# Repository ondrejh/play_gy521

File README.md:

# play GY-521
playing with GY-521 module

## msp430 receiver
connect module to MSP-EXP430G2

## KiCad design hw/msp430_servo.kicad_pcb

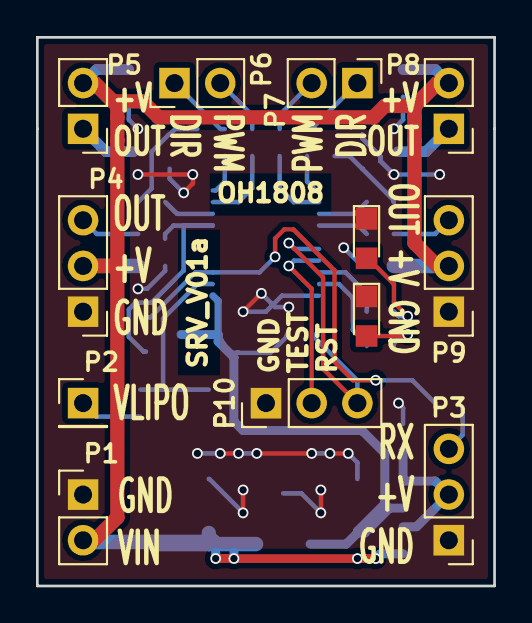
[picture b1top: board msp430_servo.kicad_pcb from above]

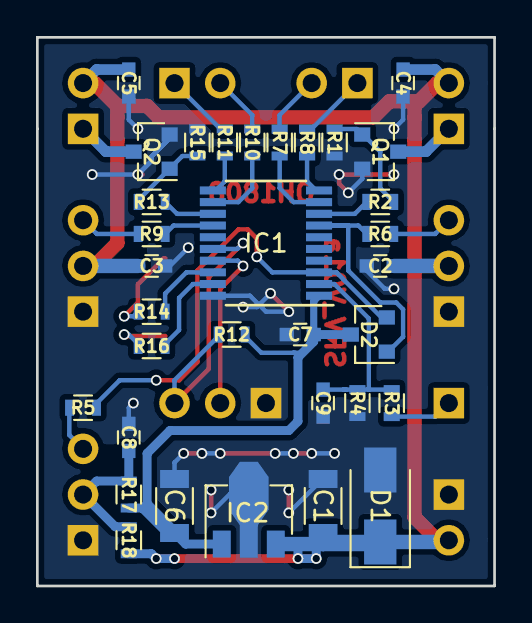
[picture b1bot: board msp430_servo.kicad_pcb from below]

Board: 2 copper layers, 25.4 x 30.5 mm, 45 parts (33 on the bottom side), 32 nets.

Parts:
C1, C6: 4u7; C_1206
C2, C3, C4, C5, C7, C8, C9: 100n; C_0603
D1: SMAJ5V0; D_SMA
D2: BAV70; SOT-23
IC1: MSP430G2553IPW20; TSSOP-20_4.4x6.5mm_Pitch0.65mm
IC2: L78L33ACUTR; SOT-89-3
LED1, LED2: Led_Small; LED_0805
P1, P5, P6, P7, P8: CONN_01X02; Pin_Header_Straight_1x02_Pitch2.54mm
P2: CONN_01X01; Pin_Header_Straight_1x01_Pitch2.54mm
P3, P4, P9, P10: CONN_01X03; Pin_Header_Straight_1x03_Pitch2.54mm
Q1, Q2: BC817-40; SOT-23
R1, R3, R12, R15: 10k; R_0603
R2, R13: 1k8; R_0603
R4: 4k7; R_0603
R5, R6: 470R; R_0603
R7, R8, R9, R10, R11: 100R; R_0603
R14, R16: 220R; R_0603
R17: 0R0; R_0603
R18: NA; R_0603

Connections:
+3V3: C6.1, C7.1, D2.3, IC1.1, IC2.1, R12.1, R17.2
+5V: C1.1, C2.1, C3.1, C4.1, C5.1, D1.1, IC2.3, P1.2, P4.2, P5.2, P8.2, P9.2, R18.2
GND: C1.2, C2.2, C3.2, C4.2, C5.2, C6.2, C7.2, C8.2, C9.2, D1.2, IC1.20, IC2.2, LED1.1, LED2.1, P1.1, P3.1, P4.1, P9.1, P10.1, Q1.2, Q2.2, R1.1, R4.1, R15.1
unnamed: C8.1, P3.2, R17.1, R18.1
unnamed: C9.1, IC1.2, R3.1, R4.2
unnamed: D2.1, IC1.7, R6.1
unnamed: D2.2, IC1.3, R5.1
unnamed: IC1.8, R2.2
unnamed: IC1.9, R7.1
unnamed: IC1.10, R8.1
unnamed: IC1.11, R11.2
unnamed: IC1.12, R10.2
unnamed: IC1.13, R13.2
unnamed: IC1.14, R9.2
unnamed: IC1.16, P10.3, R12.2
unnamed: IC1.17, P10.2
unnamed: IC1.18, R14.2
unnamed: IC1.19, R16.1
unnamed: LED1.2, R14.1
unnamed: LED2.2, R16.2
unnamed: P2.1, R3.2
unnamed: P3.3, R5.2
unnamed: P4.3, R6.2
unnamed: P5.1, Q1.3
unnamed: P6.1, R8.2
unnamed: P6.2, R7.2
unnamed: P7.1, R11.1
unnamed: P7.2, R10.1
unnamed: P8.1, Q2.3
unnamed: P9.3, R9.1
unnamed: Q1.1, R1.2, R2.1
unnamed: Q2.1, R13.1, R15.2

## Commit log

2018-03-13 python based receiver decoder
2018-03-13 fw attempt
2018-03-13 now it looks better - need test
2018-03-13 this is how it works
2018-03-15 readme update
2018-08-07 led output docu
2018-08-14 hardware
2018-08-17 TA0 outputs .. half success
2018-08-22 silk repair, assembly
2018-08-22 v01a gerber data
2018-08-24 add ch2 -> servo1, make code simplier
2018-08-24 some docu and outputs
2018-08-30 debug: beginers mistake
2018-09-16 clear project
2018-09-17 cb files
2018-09-17 i2c init
2018-09-19 uart tx buffer
2018-09-19 i2c start somehow - needs more fiddling i gues
2018-09-20 read gyro data and send it to uart
2018-09-20 cb ballast
2019-09-10 msp430fr2311 blinky example
